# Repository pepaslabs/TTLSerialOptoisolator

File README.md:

# TTLSerialOptoisolator

A board which provides isolation for a TTL serial TX / RX pair.

## License

This board design is [Open-Source Hardware](http://www.oshwa.org/definition/).  It is licensed under the [MIT License](http://opensource.org/licenses/MIT).  It was designed by Jason Pepas.

# Board design v1

Initial board design.

## Gerbers

[gerbers.zip](releases/v1/gerbers.zip)

## Schematic

[PDF](releases/v1/TTLSerialOptoisolator%20schematic.pdf).

# Design notes

## LED series resistor calculation

Can we find an LED resistor value which works for both 3.3V and 5V TTL levels?

Lite-On LTV-817 datasheet: http://media.digikey.com/pdf/Data%20Sheets/Lite-On%20PDFs/LTV-817_827_847%28M,S,S_TA1%29.pdf

The forward voltage of the LED is typically 1.2V.

* 5V - 1.2V = 3.8V
* 3.3V - 1.2V = 2.1V

Voltage|100Ω|150Ω|220Ω|330Ω|470Ω|680Ω|1kΩ
-------|----|----|----|----|----|----|---
5V|38mA|25mA|17mA|12mA|8mA|6mA|4mA
3.3V|21mA|14mA|10mA|6mA|4mA|3mA|2mA

So 330Ω would be a reasonable choice.

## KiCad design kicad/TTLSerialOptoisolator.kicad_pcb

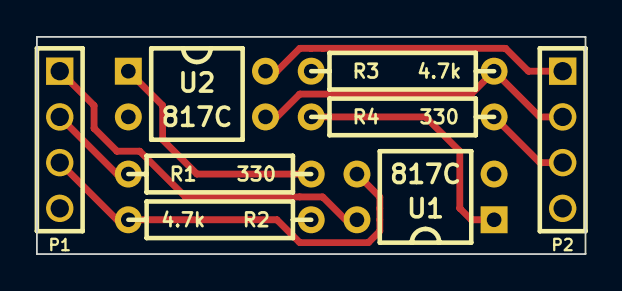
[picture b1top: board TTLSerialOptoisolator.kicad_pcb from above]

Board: 2 copper layers, 30.5 x 12.1 mm, 8 parts (0 on the bottom side), 10 nets.

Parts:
P1, P2: CONN_4; PIN_ARRAY_4x1
R1, R4: 330; R_AXIAL_0W25_059A_PL
R2, R3: 4.7k; R_AXIAL_0W25_059A_PL
U1, U2: 817C; DIP4_059A_PL

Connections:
5Va: P1.1, U1.4
5Vb: P2.1, U2.4
GNDa: P1.4, R2.1, U2.2
GNDb: P2.4, R3.1, U1.2
unnamed: R4.1, U1.1
unnamed: R1.2, U2.1
RXa: P1.3, R2.2, U1.3
RXb: P2.2, R3.2, U2.3
TXa: P1.2, R1.1
TXb: P2.3, R4.2

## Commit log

2015-04-11 creating kicad project
2015-04-11 initial opto isolator schematic
2015-04-11 initial draft of board layout
2015-04-11 iterating on board layout
2015-04-11 changing LED resistor values to 330 ohm.
2015-04-11 creating gerbers for board v1.
2015-04-11 adding board renders
2015-04-11 adding schematic for v1 release
